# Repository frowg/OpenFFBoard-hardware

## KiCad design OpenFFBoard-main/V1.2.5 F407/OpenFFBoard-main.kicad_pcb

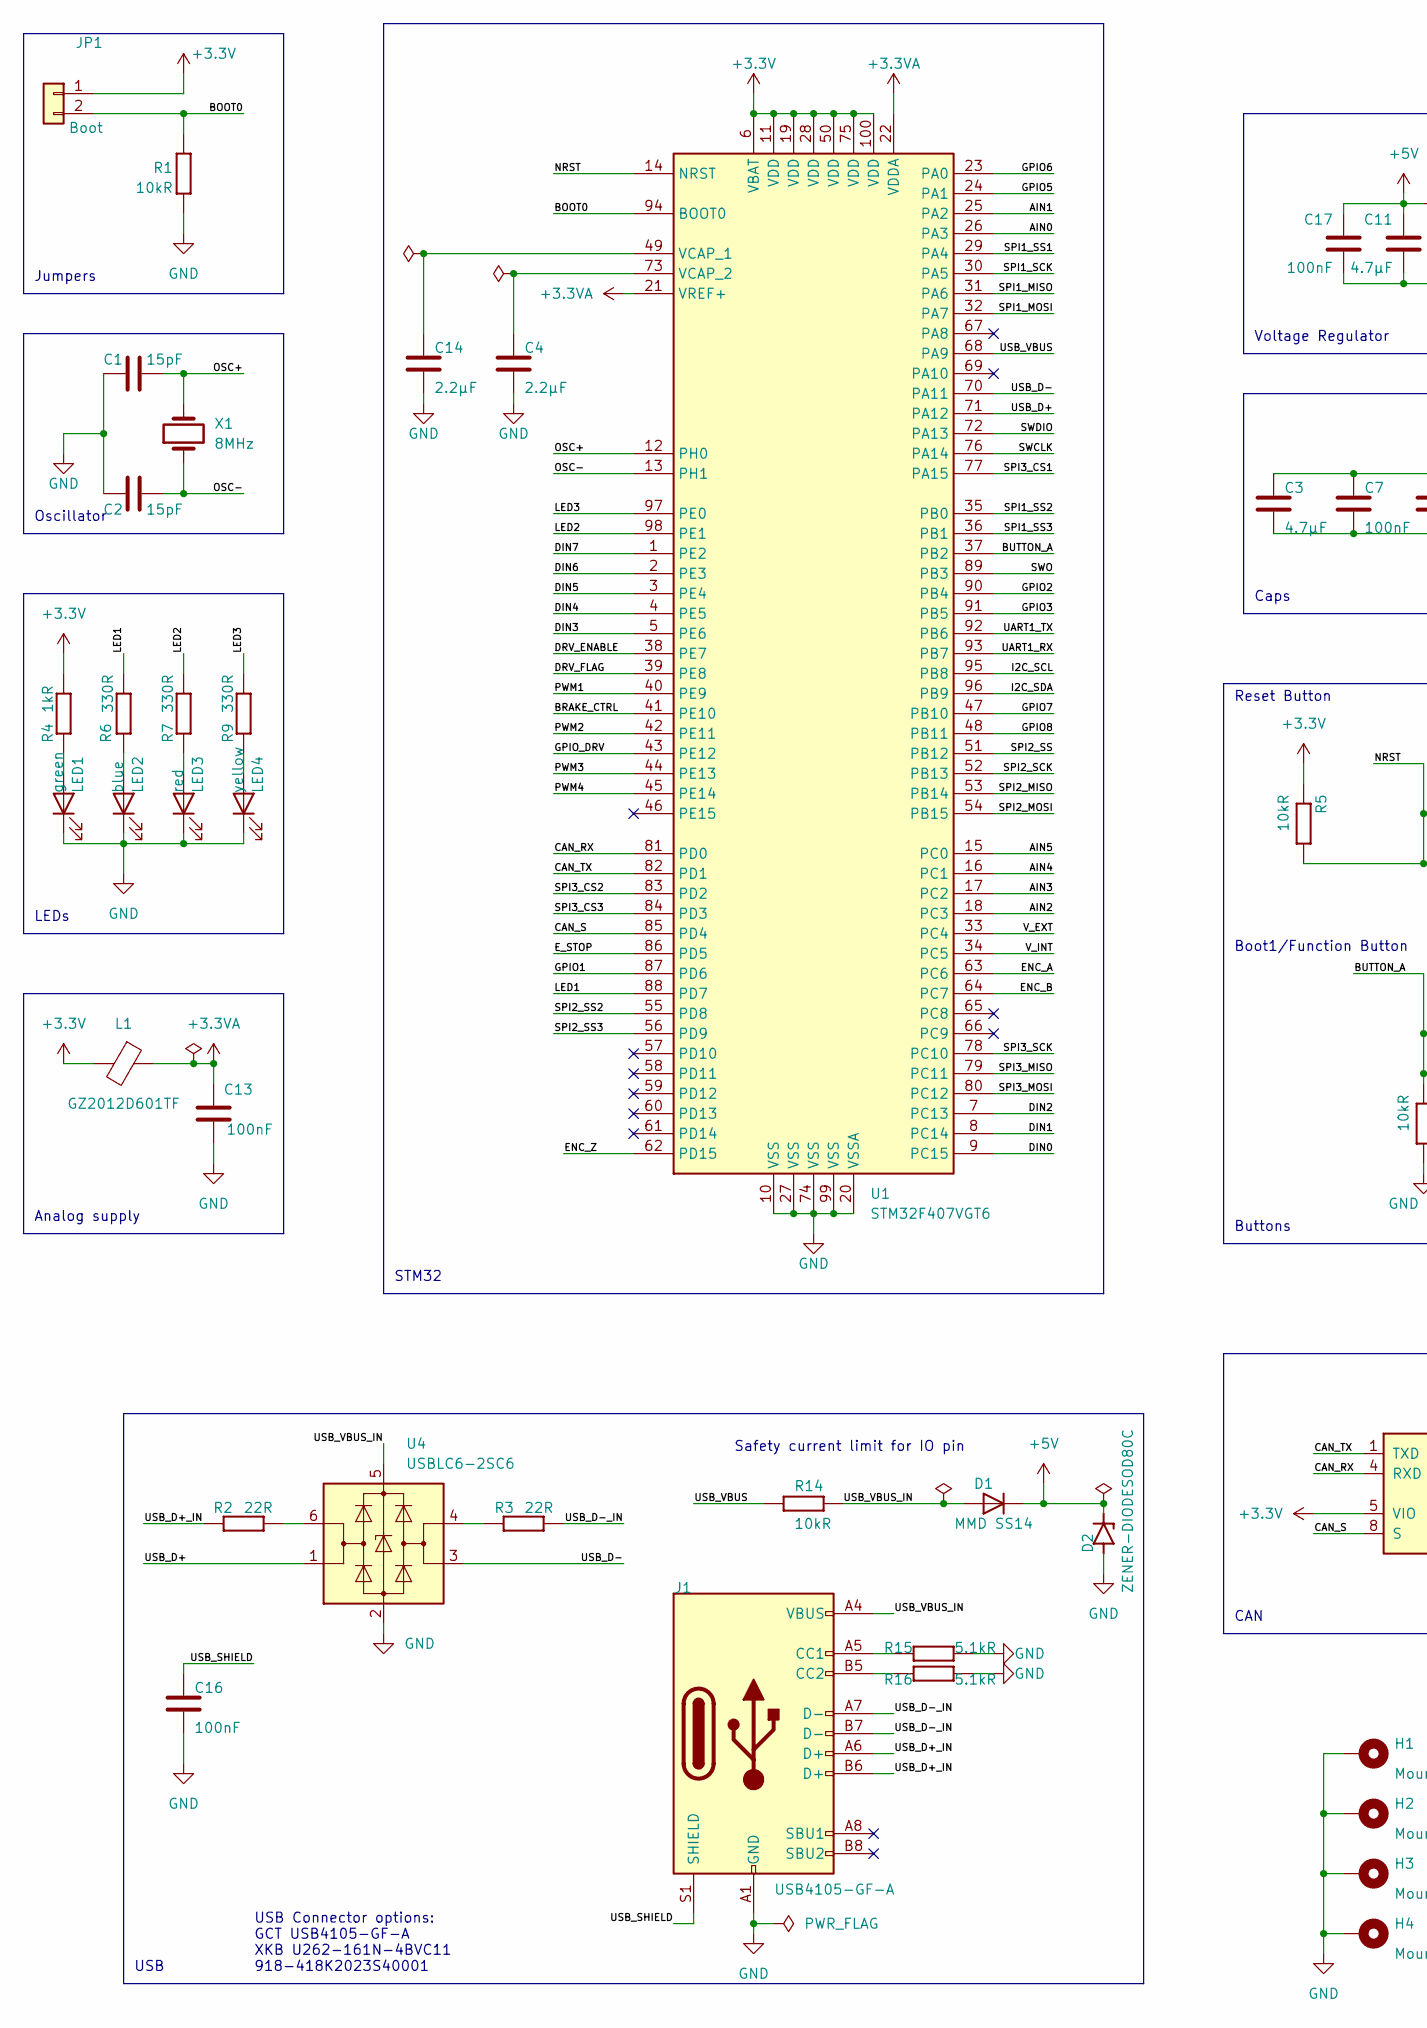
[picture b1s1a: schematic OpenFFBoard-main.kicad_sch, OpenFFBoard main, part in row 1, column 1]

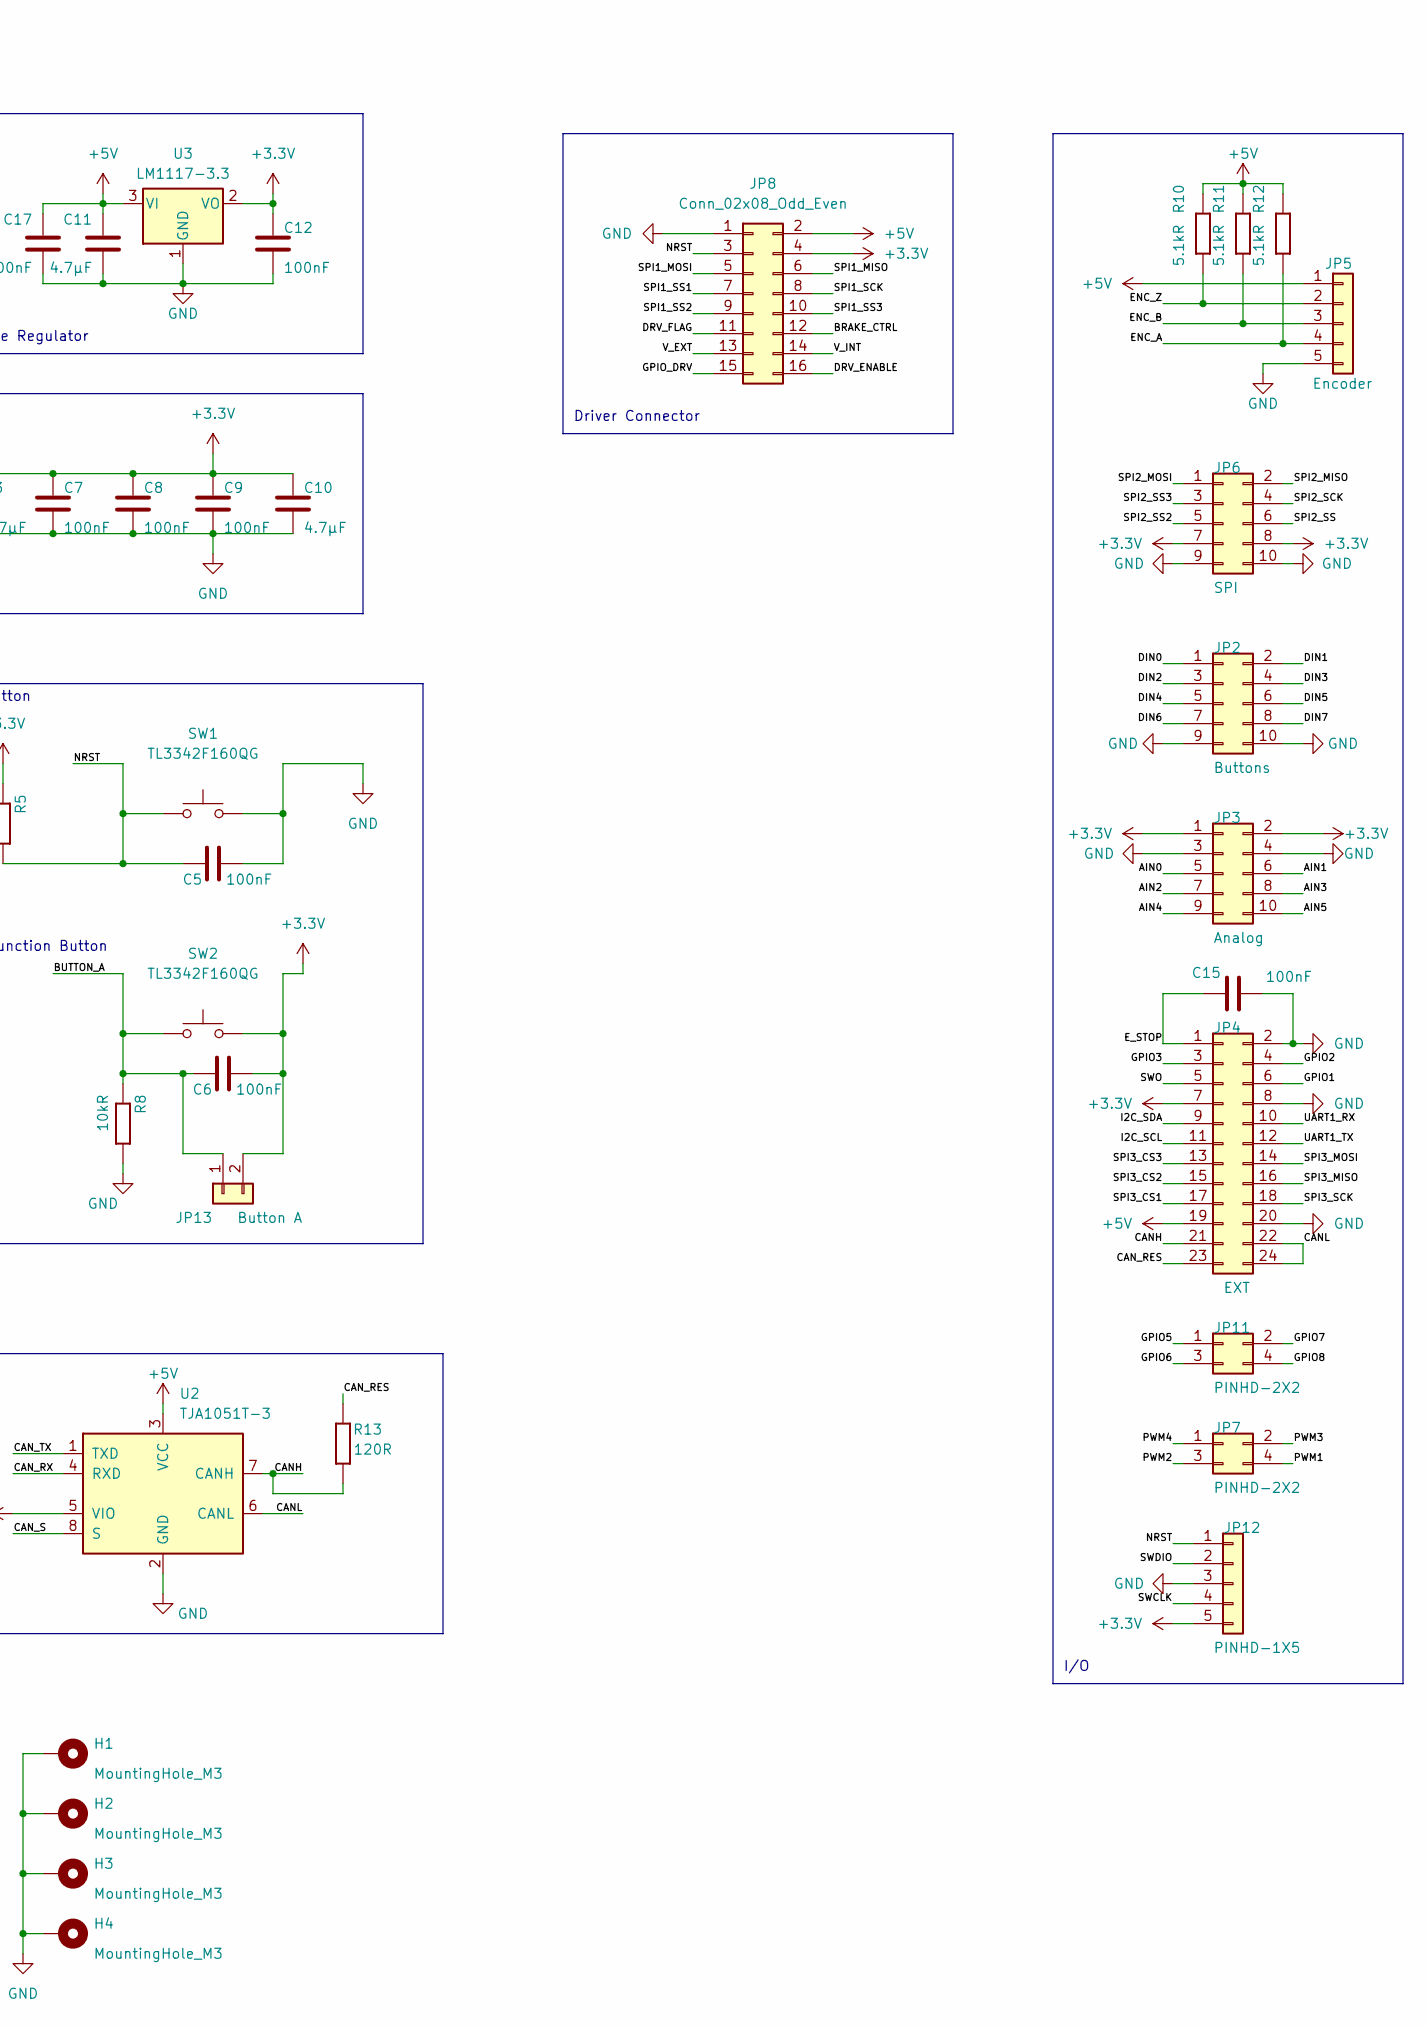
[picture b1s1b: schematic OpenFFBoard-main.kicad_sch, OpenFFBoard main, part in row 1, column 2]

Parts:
C1, C2: 15pF; C_0603_1608Metric
C3, C10, C11: 4.7µF; C_0805_2012Metric
C4, C14: 2.2µF; C_0603_1608Metric
C5, C6, C7, C8, C9, C12, C13, C15, C16, C17: 100nF; C_0603_1608Metric
D1: MMD SS14; D_SMA_Handsoldering
D2: ZENER-DIODESOD80C; SOD80C
H1, H2, H3, H4: MountingHole_M3; MountingHole_3.2mm_M3_Pad_Via
J1: USB4105-GF-A; USB_C_Receptacle_Palconn_UTC16-G
JP1: Boot; PinHeader_1x02_P2.54mm_Vertical
JP2: Buttons; PinHeader_2x05_P2.54mm_Vertical
JP3: Analog; PinHeader_2x05_P2.54mm_Vertical
JP4: EXT; PinHeader_2x12_P2.54mm_Vertical
JP5: Encoder; PinHeader_1x05_P2.54mm_Vertical
JP6: SPI; PinHeader_2x05_P2.54mm_Vertical
JP7, JP11: PINHD-2X2; PinHeader_2x02_P2.54mm_Vertical
JP8: Conn_02x08_Odd_Even; PinHeader_2x08_P2.54mm_Vertical
JP12: PINHD-1X5; PinHeader_1x05_P2.54mm_Vertical
JP13: Button A; PinHeader_1x02_P2.54mm_Vertical
L1: GZ2012D601TF; L_0805_2012Metric
LED1: green; LED_0805_2012Metric
LED2: blue; LED_0805_2012Metric
LED3: red; LED_0805_2012Metric
LED4: yellow; LED_0805_2012Metric
R1, R5, R8, R14: 10kR; R_0603_1608Metric
R2, R3: 22R; R_0603_1608Metric
R4: 1kR; R_0603_1608Metric
R6, R7, R9: 330R; R_0603_1608Metric
R10, R11, R12, R15, R16: 5.1kR; R_0603_1608Metric
R13: 120R; R_0603_1608Metric
SW1, SW2: TL3342F160QG; SW_SPST_TL3342
U1: STM32F407VGT6; LQFP-100_14x14mm_P0.5mm
U2: TJA1051T-3; SOIC-8_3.9x4.9mm_P1.27mm
U3: LM1117-3.3; SOT-223-3_TabPin2
U4: USBLC6-2SC6; SOT-23-6
X1: 8MHz; Crystal_SMD_5032-2Pin_5.0x3.2mm

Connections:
+3.3V: C3.1, C6.2, C7.1, C8.1, C9.1, C10.1, C12.1, JP1.1, JP3.1, JP3.2, JP4.7, JP6.7, JP6.8, JP8.4, JP12.5, JP13.2, L1.2, R4.2, R5.1, SW2.2, U1.6 (VBAT), U1.11 (VDD), U1.19 (VDD), U1.28 (VDD), U1.50 (VDD), U1.75 (VDD), U1.100 (VDD), U2.5 (VIO), U3.2 (VO)
+3.3VA: C13.2, L1.1, U1.21 (VREF+), U1.22 (VDDA)
+5V: C11.1, C17.2, D1.1 (K), D2.C, JP4.19, JP5.1, JP8.2, R10.1, R11.1, R12.1, U2.3 (VCC), U3.3 (VI)
/AIN0: JP3.5, U1.26 (PA3)
/AIN1: JP3.6, U1.25 (PA2)
/AIN2: JP3.7, U1.18 (PC3)
/AIN3: JP3.8, U1.17 (PC2)
/AIN4: JP3.9, U1.16 (PC1)
/AIN5: JP3.10, U1.15 (PC0)
/BOOT0: JP1.2, R1.1, U1.94 (BOOT0)
/BRAKE_CTRL: JP8.12, U1.41 (PE10)
/BUTTON_A: C6.1, JP13.1, R8.1, SW2.1, U1.37 (PB2)
/CANH: JP4.21, R13.1, U2.7 (CANH)
/CANL: JP4.22, JP4.24, U2.6 (CANL)
/CAN_RES: JP4.23, R13.2
/CAN_RX: U1.81 (PD0), U2.4 (RXD)
/CAN_S: U1.85 (PD4), U2.8 (S)
/CAN_TX: U1.82 (PD1), U2.1 (TXD)
/DIN0: JP2.1, U1.9 (PC15)
/DIN1: JP2.2, U1.8 (PC14)
/DIN2: JP2.3, U1.7 (PC13)
/DIN3: JP2.4, U1.5 (PE6)
/DIN4: JP2.5, U1.4 (PE5)
/DIN5: JP2.6, U1.3 (PE4)
/DIN6: JP2.7, U1.2 (PE3)
/DIN7: JP2.8, U1.1 (PE2)
/DRV_ENABLE: JP8.16, U1.38 (PE7)
/DRV_FLAG: JP8.11, U1.39 (PE8)
/ENC_A: JP5.4, R12.2, U1.63 (PC6)
/ENC_B: JP5.3, R11.2, U1.64 (PC7)
/ENC_Z: JP5.2, R10.2, U1.62 (PD15)
/E_STOP: C15.1, JP4.1, U1.86 (PD5)
/GPIO1: JP4.6, U1.87 (PD6)
/GPIO2: JP4.4, U1.90 (PB4)
/GPIO3: JP4.3, U1.91 (PB5)
/GPIO5: JP11.1, U1.24 (PA1)
/GPIO6: JP11.3, U1.23 (PA0)
/GPIO7: JP11.2, U1.47 (PB10)
/GPIO8: JP11.4, U1.48 (PB11)
/GPIO_DRV: JP8.15, U1.43 (PE12)
/I2C_SCL: JP4.11, U1.95 (PB8)
/I2C_SDA: JP4.9, U1.96 (PB9)
/LED1: R6.2, U1.88 (PD7)
/LED2: R7.2, U1.98 (PE1)
/LED3: R9.2, U1.97 (PE0)
/NRST: C5.1, JP8.3, JP12.1, R5.2, SW1.1, U1.14 (NRST)
/OSC+: C1.2, U1.12 (PH0), X1.2
/OSC-: C2.2, U1.13 (PH1), X1.1
/PWM1: JP7.4, U1.40 (PE9)
/PWM2: JP7.3, U1.42 (PE11)
/PWM3: JP7.2, U1.44 (PE13)
/PWM4: JP7.1, U1.45 (PE14)
/SPI1_MISO: JP8.6, U1.31 (PA6)
/SPI1_MOSI: JP8.5, U1.32 (PA7)
/SPI1_SCK: JP8.8, U1.30 (PA5)
/SPI1_SS1: JP8.7, U1.29 (PA4)
/SPI1_SS2: JP8.9, U1.35 (PB0)
/SPI1_SS3: JP8.10, U1.36 (PB1)
/SPI2_MISO: JP6.2, U1.53 (PB14)
/SPI2_MOSI: JP6.1, U1.54 (PB15)
/SPI2_SCK: JP6.4, U1.52 (PB13)
/SPI2_SS: JP6.6, U1.51 (PB12)
/SPI2_SS2: JP6.5, U1.55 (PD8)
/SPI2_SS3: JP6.3, U1.56 (PD9)
/SPI3_CS1: JP4.17, U1.77 (PA15)
/SPI3_CS2: JP4.15, U1.83 (PD2)
/SPI3_CS3: JP4.13, U1.84 (PD3)
/SPI3_MISO: JP4.16, U1.79 (PC11)
/SPI3_MOSI: JP4.14, U1.80 (PC12)
/SPI3_SCK: JP4.18, U1.78 (PC10)
/SWCLK: JP12.4, U1.76 (PA14)
/SWDIO: JP12.2, U1.72 (PA13)
/SWO: JP4.5, U1.89 (PB3)
/UART1_RX: JP4.10, U1.93 (PB7)
/UART1_TX: JP4.12, U1.92 (PB6)
/USB_D+: U1.71 (PA12), U4.1 (I/O1)
/USB_D+_IN: J1.A6 (D+), J1.B6 (D+), R2.2
/USB_D-: U1.70 (PA11), U4.3 (I/O2)
/USB_D-_IN: J1.A7 (D-), J1.B7 (D-), R3.2
/USB_SHIELD: C16.1, J1.S1 (SHIELD)
/USB_VBUS: R14.1, U1.68 (PA9)
/USB_VBUS_IN: D1.2 (A), J1.A4 (VBUS), J1.A9 (VBUS), J1.B4 (VBUS), J1.B9 (VBUS), R14.2, U4.5 (VBUS)
/V_EXT: JP8.13, U1.33 (PC4)
/V_INT: JP8.14, U1.34 (PC5)
GND: C1.1, C2.1, C3.2, C4.2, C5.2, C7.2, C8.2, C9.2, C10.2, C11.2, C12.2, C13.1, C14.2, C15.2, C16.2, C17.1, D2.A, H1.1, H2.1, H3.1, H4.1, J1.A1 (GND), J1.A12 (GND), J1.B1 (GND), J1.B12 (GND), JP2.9, JP2.10, JP3.3, JP3.4, JP4.2, JP4.8, JP4.20, JP5.5, JP6.9, JP6.10, JP8.1, JP12.3, LED1.1 (K), LED2.1 (K), LED3.1 (K), LED4.1 (K), R1.2, R8.2, R15.1, R16.2, SW1.2, U1.10 (VSS), U1.20 (VSSA), U1.27 (VSS), U1.74 (VSS), U1.99 (VSS), U2.2 (GND), U3.1 (GND), U4.2 (GND)
unnamed: C4.1, U1.73 (VCAP_2)
unnamed: C14.1, U1.49 (VCAP_1)
unnamed: J1.A5 (CC1), R15.2
unnamed: J1.B5 (CC2), R16.1
unnamed: LED1.2 (A), R4.1
unnamed: LED2.2 (A), R6.1
unnamed: LED3.2 (A), R7.1
unnamed: LED4.2 (A), R9.1
unnamed: R2.1, U4.6 (I/O1)
unnamed: R3.1, U4.4 (I/O2)

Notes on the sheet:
Safety current limit for IO pin
Voltage Regulator
USB Connector options: GCT USB4105-GF-A XKB U262-161N-4BVC11 918-418K2023S40001
I/O
Analog supply
Jumpers
CAN
Reset Button
Driver Connector
Oscillator
STM32
Buttons
Boot1/Function Button
USB
Caps
LEDs

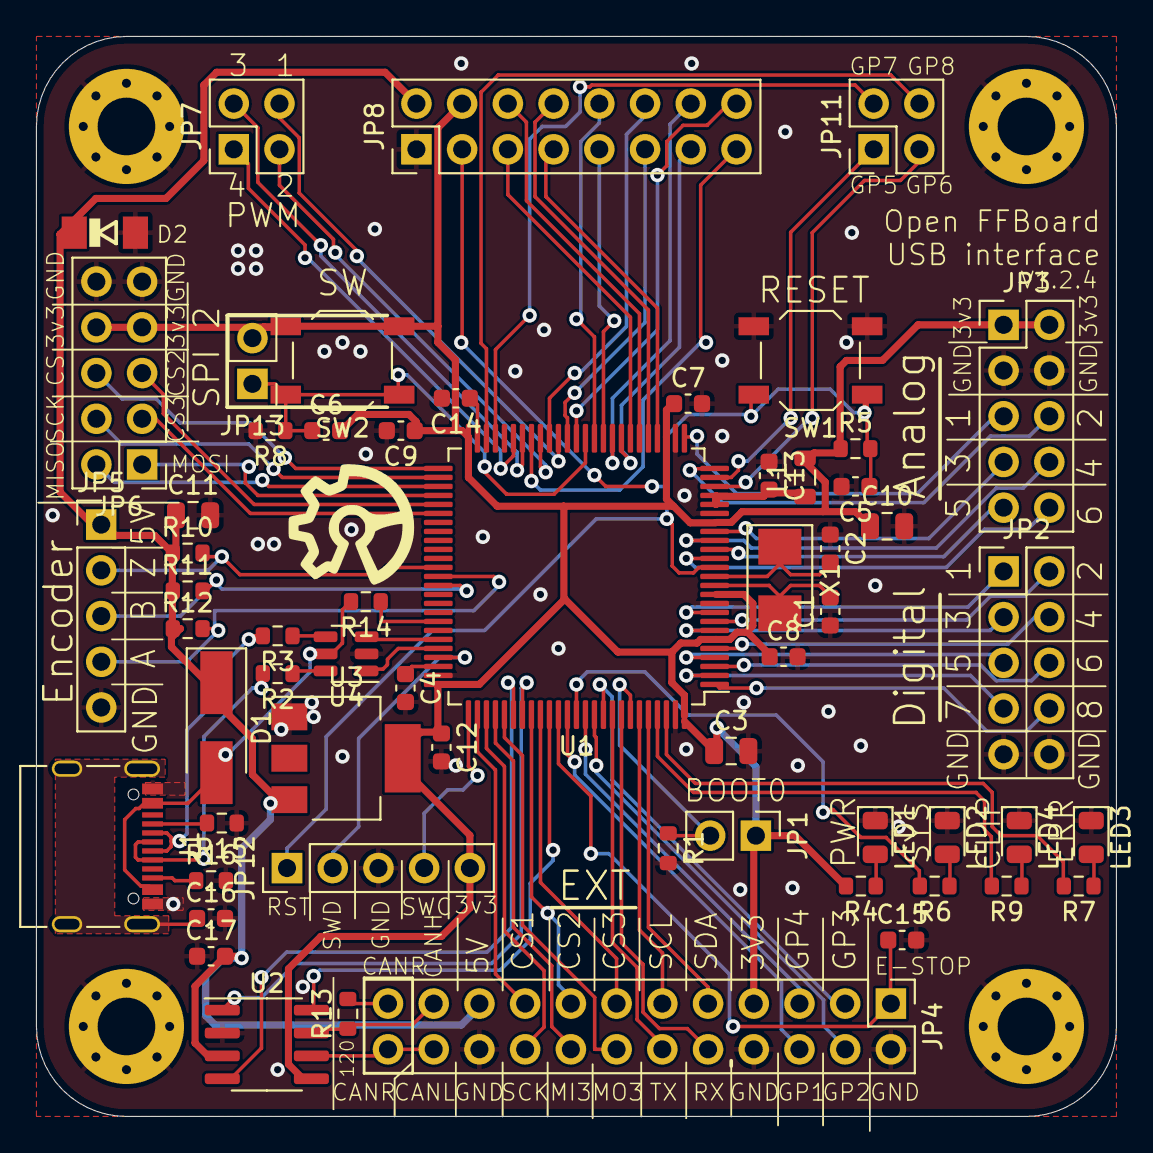
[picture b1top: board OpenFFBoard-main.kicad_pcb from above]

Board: 4 copper layers, 60.0 x 60.0 mm, 63 parts (0 on the bottom side), 95 nets.

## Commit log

2023-01-03 First commit of 1.2.5 board version
2023-01-09 defined net class rules and added missing 3d models
